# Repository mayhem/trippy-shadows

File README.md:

# trippy-shadows
Code for trippy shadows project

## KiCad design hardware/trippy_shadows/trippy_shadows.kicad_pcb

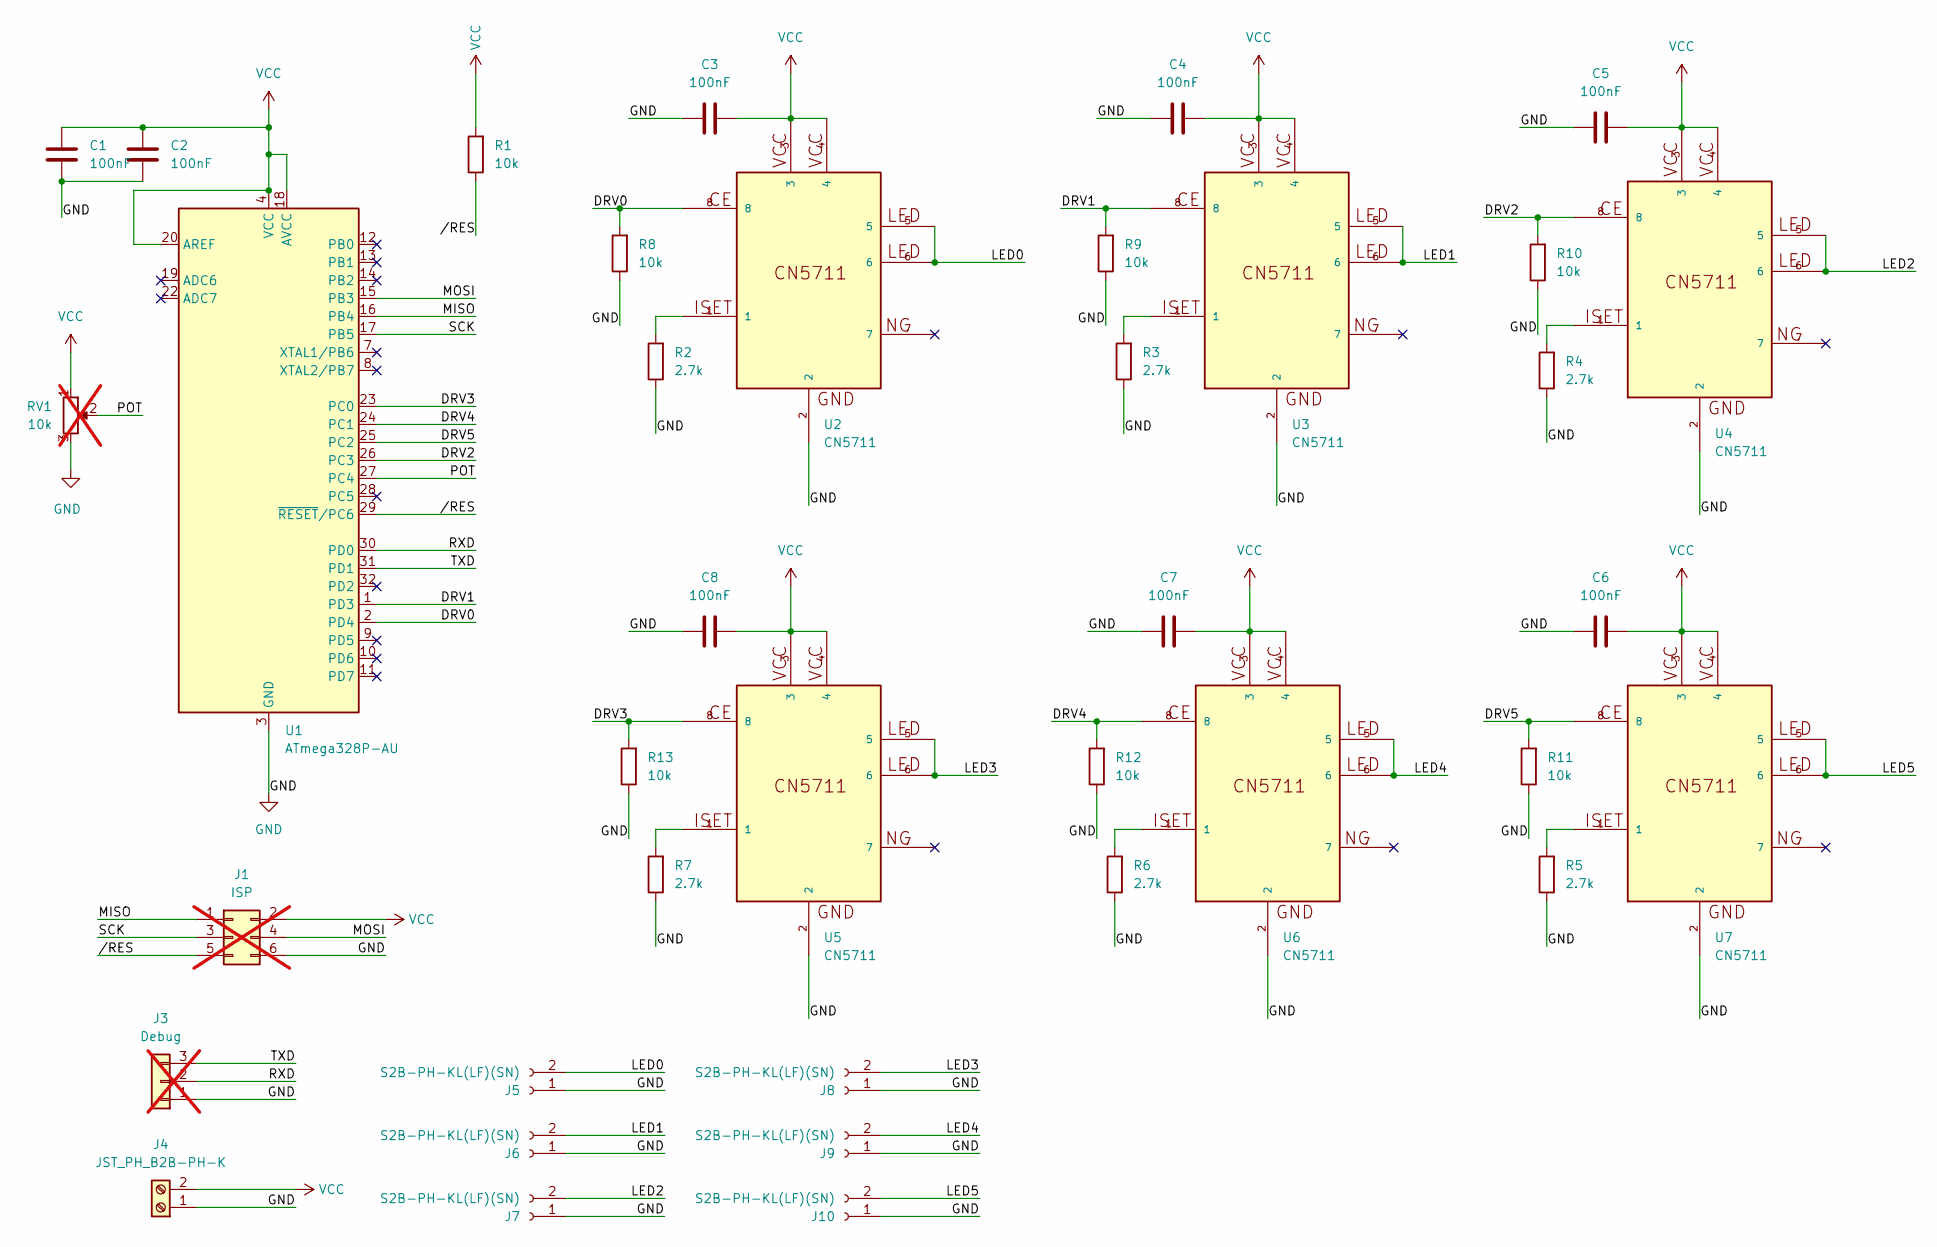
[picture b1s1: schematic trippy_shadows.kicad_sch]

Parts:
C1, C2, C3, C4, C5, C6, C7, C8: 100nF; C_0805_2012Metric
J1: ISP; PinHeader_2x03_P2.54mm_Vertical; not fitted
J3: Debug; PinHeader_1x03_P2.54mm_Vertical; not fitted
J4: JST_PH_B2B-PH-K; JST_PH_B2B-PH-K_1x02_P2.00mm_Vertical
J5, J6, J7, J8, J9, J10: S2B-PH-KL(LF)(SN); JST_PH_S2B-PH-K_1x02_P2.00mm_Horizontal
R1, R8, R9, R10, R11, R12, R13: 10k; R_0805_2012Metric
R2, R3, R4, R5, R6, R7: 2.7k; R_0805_2012Metric
RV1: 10k; Potentiometer_Alps_RK09K_Single_Vertical; not fitted
U1: ATmega328P-AU; TQFP-32_7x7mm_P0.8mm
U2, U3, U4, U5, U6, U7: CN5711; SOIC-8-1EP_3.9x4.9mm_P1.27mm_EP2.41x3.3mm_ThermalVias

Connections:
/DRV0: R8.2, U1.2 (PD4), U2.8
/DRV1: R9.2, U1.1 (PD3), U3.8
/DRV2: R10.2, U1.26 (PC3), U4.8
/DRV3: R13.2, U1.23 (PC0), U5.8
/DRV4: R12.2, U1.24 (PC1), U6.8
/DRV5: R11.2, U1.25 (PC2), U7.8
/LED0: J5.2, U2.5, U2.6
/LED1: J6.2, U3.5, U3.6
/LED2: J7.2, U4.5, U4.6
/LED3: J8.2, U5.5, U5.6
/LED4: J9.2, U6.5, U6.6
/LED5: J10.2, U7.5, U7.6
/MISO: J1.1, U1.16 (PB4)
/MOSI: J1.4, U1.15 (PB3)
/POT: RV1.2, U1.27 (PC4)
/RXD: J3.2, U1.30 (PD0)
/SCK: J1.3, U1.17 (PB5)
/TXD: J3.3, U1.31 (PD1)
//RES: J1.5, R1.1, U1.29 (~RESET/PC6)
GND: C1.2, C2.2, C3.1, C4.1, C5.1, C6.1, C7.1, C8.1, J1.6, J3.1, J4.1, J5.1, J6.1, J7.1, J8.1, J9.1, J10.1, R2.1, R3.1, R4.1, R5.1, R6.1, R7.1, R8.1, R9.1, R10.1, R11.1, R12.1, R13.1, RV1.3, U1.3 (GND), U1.5 (GND), U1.21 (GND), U2.2, U3.2, U4.2, U5.2, U6.2, U7.2
unnamed: R2.2, U2.1
unnamed: R3.2, U3.1
unnamed: R4.2, U4.1
unnamed: R5.2, U7.1
unnamed: R6.2, U6.1
unnamed: R7.2, U5.1
VCC: C1.1, C2.1, C3.2, C4.2, C5.2, C6.2, C7.2, C8.2, J1.2, J4.2, R1.2, RV1.1, U1.4 (VCC), U1.6 (VCC), U1.18 (AVCC), U1.20 (AREF), U2.3, U2.4, U3.3, U3.4, U4.3, U4.4, U5.3, U5.4, U6.3, U6.4, U7.3, U7.4

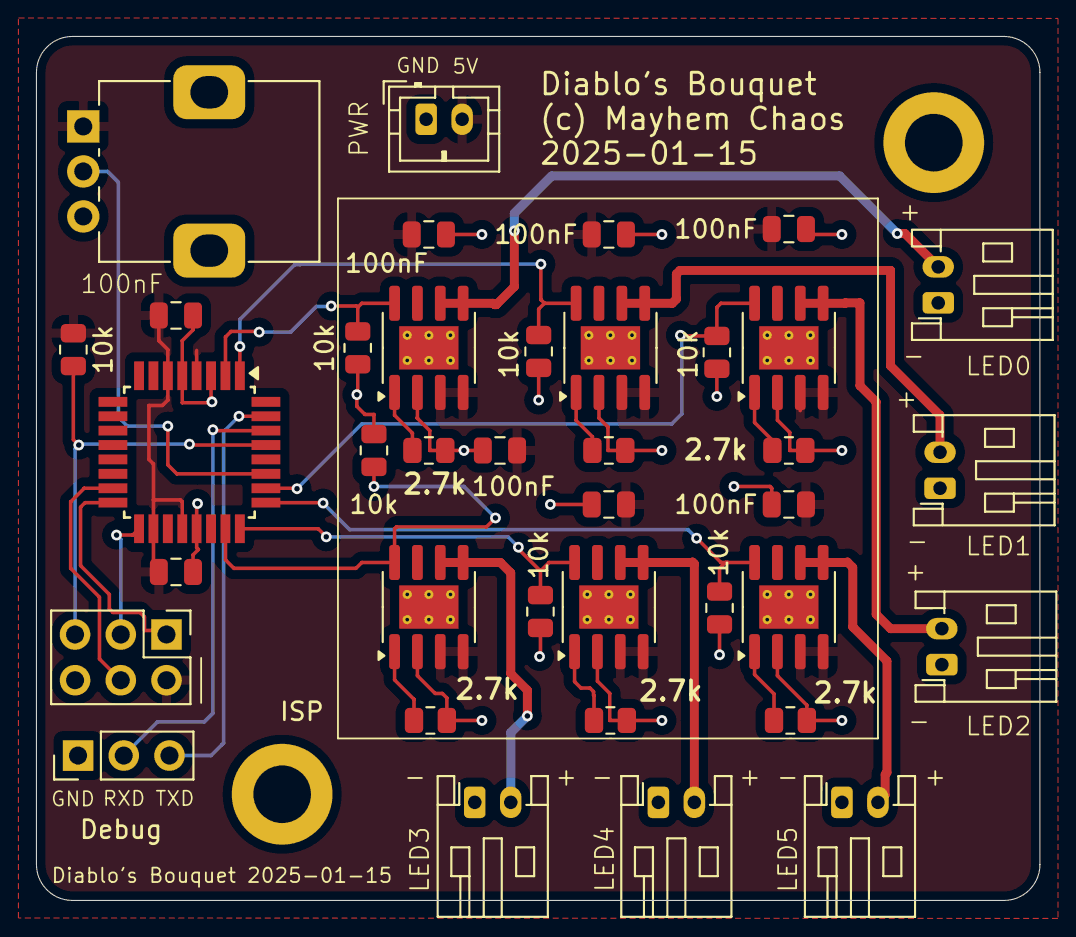
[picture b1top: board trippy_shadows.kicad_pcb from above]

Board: 2 copper layers, 55.8 x 48.0 mm, 38 parts (0 on the bottom side), 27 nets.

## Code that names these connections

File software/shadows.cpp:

#include <avr/io.h>
#include <util/delay.h>
#include <stdio.h>

#define TRIGPOINT 128

#define BAUD             9600
#define UBBR             (F_CPU / 16 / BAUD - 1)

void serial_init(void)
{
    /*Set baud rate */ 
    UBRR0H = (unsigned char)(UBBR>>8); 
    UBRR0L = (unsigned char)UBBR; 
    /* Enable transmitter */ 
    UCSR0B = (1<<TXEN0) | (1<<RXEN0); 
    /* Set frame format: 8data, 1stop bit */ 
    UCSR0C = (0<<USBS0)|(3<<UCSZ00); 
}

void serial_tx(uint8_t ch)
{
    while ( !( UCSR0A & (1<<UDRE0)) );
    UDR0 = ch;
}

void dprint(const char *ptr)
{
    for(; *ptr; ptr++)
    {
        if (*ptr == '\n') serial_tx('\r');
        serial_tx(*ptr);
    }
}

void adc_config(uint8_t ch){
    // Set ADC configuration registers as follows:
    // ADMUX - ADC multiplexer selection register: 
        // REFS0 = 1        - AVcc reference with external capacitor at AREF pin
        // ADLAR = 1        - ADC presentation of ADC result (left adjusted)
    // ADCSRA - ADC control and status register A
        // ADATE = 1        - Enable auto triggering of the ADC
        // ADPS0, ADPS1, ADPS2 = 1 - Set the division factor between the system clock frequency and the input clock to the ADC (/128 - 62.5kHz)
//    ADMUX |= (1 << REFS0) | (1 << ADLAR);
    ADMUX |= (1 << ADLAR);
    switch(ch){
        case 6:
            // MUX1, MUX2 = 1   - Choose the ADC channel 6
            ADMUX |= (1<< MUX2) | (1 << MUX1);
            break;
        case 7:
            // MUX0, MUX1, MUX2 = 1   - Choose the ADC channel 7
            ADMUX |= (1 << MUX2) | (1 << MUX1) | (1 << MUX0);
            break;
    }
    ADCSRA |= (1 << ADPS2) | (1 << ADPS1) | (1 << ADATE);

    // enabled the adc
    ADCSRA |= (1 << ADEN);
}

int main(void)
{
    serial_init();
    adc_config(7);

    dprint("Hello!\n");

	// Main program loop
    while (1) 
    {
		// Start an ADC conversion by setting ADSC bit (bit 6)
		ADCSRA = ADCSRA | (1 << ADSC);
		
		// Wait until the ADSC bit has been cleared
		while(ADCSRA & (1 << ADSC));

        int h = ADCH;
        int l = ADCL;
        char text[32];
        sprintf(text, "%d,%d\n", l, h);
        dprint(text);
	}
}


#if 0

#include <avr/io.h>
#include <util/delay.h>

// For Version 2024-12-23 of this board
// LED0 -> PC0
// LED1 -> PC1
// LED2 -> PC2
// LED3 -> PC3
// LED4 -> PD3
// LED5 -> PD4

#define LED0 0
#define LED1 1
#define LED2 2
#define LED3 3
#define LED4 3
#define LED5 4

// Bit manipulation macros
#define sbi(a, b) ((a) |= 1 << (b))       //sets bit B in variable A
#define cbi(a, b) ((a) &= ~(1 << (b)))    //clears bit B in variable A
#define tbi(a, b) ((a) ^= 1 << (b))       //toggles bit B in variable A

int _main(void)
{
    uint8_t i;
    
    DDRC = _BV(LED0) | _BV(LED1) | _BV(LED2) | _BV(LED3);
    DDRD = _BV(LED4) | _BV(LED5);

    cbi(PORTC, 0);
    cbi(PORTC, 1);
    cbi(PORTC, 2);
    cbi(PORTC, 3);
    cbi(PORTD, 3);
    cbi(PORTD, 4);
    for(;;)
        for(i = 0; i < 6; i++)
        {
            if (i < 4)
                sbi(PORTC, i);
            else
                sbi(PORTD, i - 1);

            _delay_ms(50);

            if (i < 4)
                cbi(PORTC, i);
            else
                cbi(PORTD, i - 1);
        }
    
    return 0;
}
#endif

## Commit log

2024-12-23 Add circuit board and simple software
2025-01-02 Working on new board!
2025-01-06 Commit latest board design
2025-01-15 Updated schematic to move to working adc
2025-01-15 Ardunio software works!
2025-01-15 Take out unneeded comms
